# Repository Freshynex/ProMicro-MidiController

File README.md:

# Pro Micro Midi Controller

## 1. A projekt bemutatása
### 1.1 Általános leírás
Ez a projekt a zenekészítés/zeneszerzés folyamatát segíti a MIDI protokoll felhasználásával.
Ennek a készüléknek a felépítése különböző feladatott ellátó alrészekből áll.

### 1.2 Vezérlő és modulok

A legfőbb része egy Atmel ATMEGA32u4 ic-vel ellátott Arduino Pro Micro fejlesztői alaplap (továbbiakban MCU).
Az MCU-t egy kifejtő-kártyára helyezve a többi alrész (továbbiakban modul) ráköthető.

A kifejtőkártya:

A következő modulok vannak integrálva a készülékben:

 - Kijelző modul (továbbiakban <b>DISP</b>), amely egy egyszerű interfészt biztosít, hogy az aktuális bemeneti
értékeket visszaadja, illetve hogy kényelmesen lehessen konfigurálni azt.

 - Oktáv-váltó modul (továbbiakban <b>OCTSTP</b>), amely egyszerű elérhetőséget ad oktáv-léptetéshez
  
 - Analóg modul (továbbiakban <b>ANAL</b>), egy olyan felület amely kihasználja az MCU saját analog bemeneteit, és
visszaad egy értéket.

 - Billentyűzet modul (továbbiakban <b>KB</b>), amely egy 2 oktávos zongora interfészt ad a felhasználónak. 

## 2. Alkatrészek és kapcsolás

### 2.1 Főalkatrészek

MCU: Arduino Pro Micro Atmel ATMEGA32u4

DISP: 128x64 i2c oled display (SSD1306 driver)

Oktáv váltó gombok: TACTS-6x6x7.3 (2 db)

KB gombok: AKKO Stellar Rose Switch – Lubed-5pin (24 db)

Tengelyes potméter: POM1615 LIN 1K B (2 db)

Toló potméter: PTA2043-2015CIB203 (2 db)

PISO shift register: 74HC166 (3 db)

### 2.1 Kapcsolás rajz

## 3. Funkcionalitás
 Teszteléshez használt szoftver: FL Studio 20 (Macbook M1-en kicsit bugos, ezért a kép villódzik néha)

### 3.1 MIDI Protokoll

A MIDI protokollban 8 bites adatcsomagokkal dolgozunk. Két féle üzenet van: status és data. Az első bit azt jelöli, hogy a kettő közül melyiket küldjük, így adat üzenet esetén 0-127, command üzenet esetén 128-255 a használható értéktartomány. Ezek együttesen alkotnak egy midi üzenetet (message).

Egy üzenet mindig status byte-tal kezdődik, amit a parancs függvényében 0, 1 vagy 2 data byte követ.
A status byte felső 4 bitje jelöli a kiadott parancsot (aminek az első bitje mindig 1, így az első kódszó decimálisan a 8), a második fele a csatornát jelöli (16 csatornát lehet kezelni, ebben a projektben egynél többre nincs szükségünk).

Számunkra fontosabb status üzenetek:

| Status üzenet  | Üzenet kódja | Adat byte 1 | Adat byte 2 | Adat byte 3 |
| -------------  | ------------ | ----------- | ----------- | ----------- |
| NoteOn         | 0x90         | Pitch       | Velocity    |             |
| NoteOff        | 0x80         | Pitch       | Velocity    |             |
| Control Change | 0xB0         | CC number   | MSB         | LSB *       | 

 *<sub> Adat byte 3 (LSB) nem kötelező, de 7 helyett 14 bit pontosságu értéket adhatunk meg vele </sub>

### 3.2 Billentyűzet

A billentyűzet kialakítása egy zongora mintájára készült. 2 oktáv, ami 24 gomb. A gombok mechanikus billentyűkapcsolókkal vannak kivitelezve. A keret illetve gomb kupakok 3D nyomtatással készültek. Három kaszkádolt parallel in serial out shift register segítségével vannak az MCU-ra kötve, így csak 3 pin felhasználása szükséges. Ez a fajta megoldás lehetővé teszi hogy 3Byte-on visszakapjuk a gombok állapotát egyszerre.

### 3.3 Oktáv váltás

A zenekészítéshez szükséges, hogy a billentyűzet képes legyen több oktávon is játszani. Ehhez az <b>MCU</b> két digitális bemenetét használjuk. A készülék oktáv-váltó gombok hatására a billentyűzeten reprezentált 2 oktávot eltolja, és így mind a 10 MIDI protokollban használt oktáv elérhető.

### 3.4 Analog bevitel

Kettő forgatható és kettő tolható lineáris potméter segítségével, kihasználva Kirchoff törvényeit, képes a készülék adott csatornák állapotait módosítani. A választott <b>MCU</b> analog bemenetei a referencia feszültséghez képest adja vissza a bemeneti értéket. Ezt a készülék 0-1023-as intervallumban elhelyezi (map-eli).

Ez a következő képpen nyílvánul meg:
| Ref. V         | ANAL bemenet | Érték       |
| -------------  | ------------ | ----------- |
|       5V       | 0V           | 0           |
|       -"-      | 2.5V         | 512         |
|       -"-      | 5V           | 1023        |

### 3.5 i²c Kijelző és protokol

Az i²c, egy olyan protokoll, amely MASTER-SLAVE kapcsolatot biztosít <u>kettő vagy több</u> eszköz között. A szállítandó adatot a protokoll címkézi és szállítja az adatvonalon.
Amikor a SLAVE címe egyezik a csomagban elhelyezett célcímmel, akkor azt a SLAVE fogadja és feldogozza. 

A készülék rendelkezik egy kis 1.2"-es OLED kijelző, amely SSD1306-os meghajtású. Jelenleg a <b>DISP</b> beépített címmel rendelkezik, amelynek a módosítása nehézkes.
A mostani címe <b>0x78</b>.

## 4. Bővithetőség
### 4.1 I²C (Inter-Integrated Circuit)

Az <b>MCU</b>-nak nem az összes pin-jét használtuk, ezért ezekre még kapcsolhatóak eszközök. Amennyiben a beépítendő eszköz i²c-vel kommunikál, így az ráközhető párhuzamosan ugyanarra az ágra, amelyiken rajta van a <b>DISP</b>. Ebben az esetben érdemes figyelni a rákötendő eszköz <u><b>címére</b></u>. Amennyiben a címeknél ütközés történik, úgy nem fog működik a ráhelyezett eszköz, illetve a <b>DISP</b>.

Lehetséges bővítési lehetőségek a jelzett protokollon:
| IC / MODUL név | Funkció                  |
| -------------  | ------------------------ |
|  ADS1115 / -M  | ANAL bővítő (A0 - A3)    |
|PCF8574 / IN830S| DIGITAL bővítő (8db, be) |
|PCF8574 / OC805S| DIGITAL bővítő (8db, ki) |

### 4.2 UART (Universal Asynchronous Receiver-Transmitter)

Az UART egy olyan soron protokoll fajta, amely két egyenrangú eszközt köt össze. Bekötéséhez egy adó, egy fogadó és közös test szükséges. Ez a protokoll a közlendő információt egy start- és stop-bittel ellátott bitfolyammá alakítja.
Ehhez a fajta kapcsolathoz nem szükséges külön órajel, mivel a kommunikációt egy közösen előre deklarált jelaránnyal (baudrate) éri el. A Küldő fél a bitfolyamot a saját Tx (Transmit) ágán küldi a másik eszköz Rx (Receive lábára.
Ez igaz fordítottan is, ezért ez a fajta megoldás Full-Duplex-nek minősül.
| A eszköz | B eszköz |
|----------|----------|
|    Tx    |    Rx    |
|    Rx    |    Tx    |
|    G     |    G     |
|   *Vcc   |   *Vcc   |

*<sub>Ha a másik készülék rendelkezik saját táp-ellátással, akkor a Vcc összekötése nem szükséges.</sub>

## 5. Készülék Prezentáció és Demo

### Billentyűzet
https://github.com/user-attachments/assets/6a722bac-2a85-4638-812b-2556ad7aba79

### Potméter
[<video src="_vids/Pot_demo.mp4" width="320" height="240" controls></video>
](https://github.com/user-attachments/assets/77403d33-6a48-4602-aa05-ce928a655359
)
### Billentyűzet, potméter (pitch paraméter állítása), oktáv váltás
https://github.com/user-attachments/assets/33ad1122-0a03-4d51-aa62-576f443cc43e

### 3D render

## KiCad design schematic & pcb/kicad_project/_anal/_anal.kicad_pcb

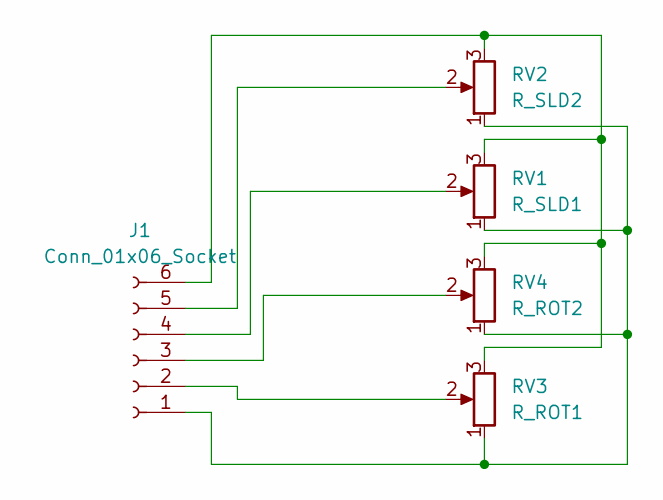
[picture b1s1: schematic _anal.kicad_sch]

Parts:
J1: Conn_01x06_Socket; PinSocket_1x06_P2.54mm_Vertical
RV1: R_SLD1; Potentiometer_Bourns_PTA4543_Single_Slide
RV2: R_SLD2; Potentiometer_Bourns_PTA4543_Single_Slide
RV3: R_ROT1; PinSocket_1x03_P2.54mm_Vertical
RV4: R_ROT2; PinSocket_1x03_P2.54mm_Vertical

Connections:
unnamed: J1.1, RV1.1, RV2.1, RV3.1, RV4.1
unnamed: J1.2, RV3.2
unnamed: J1.3, RV4.2
unnamed: J1.4, RV1.2
unnamed: J1.5, RV2.2
unnamed: J1.6, RV1.3, RV2.3, RV3.3, RV4.3

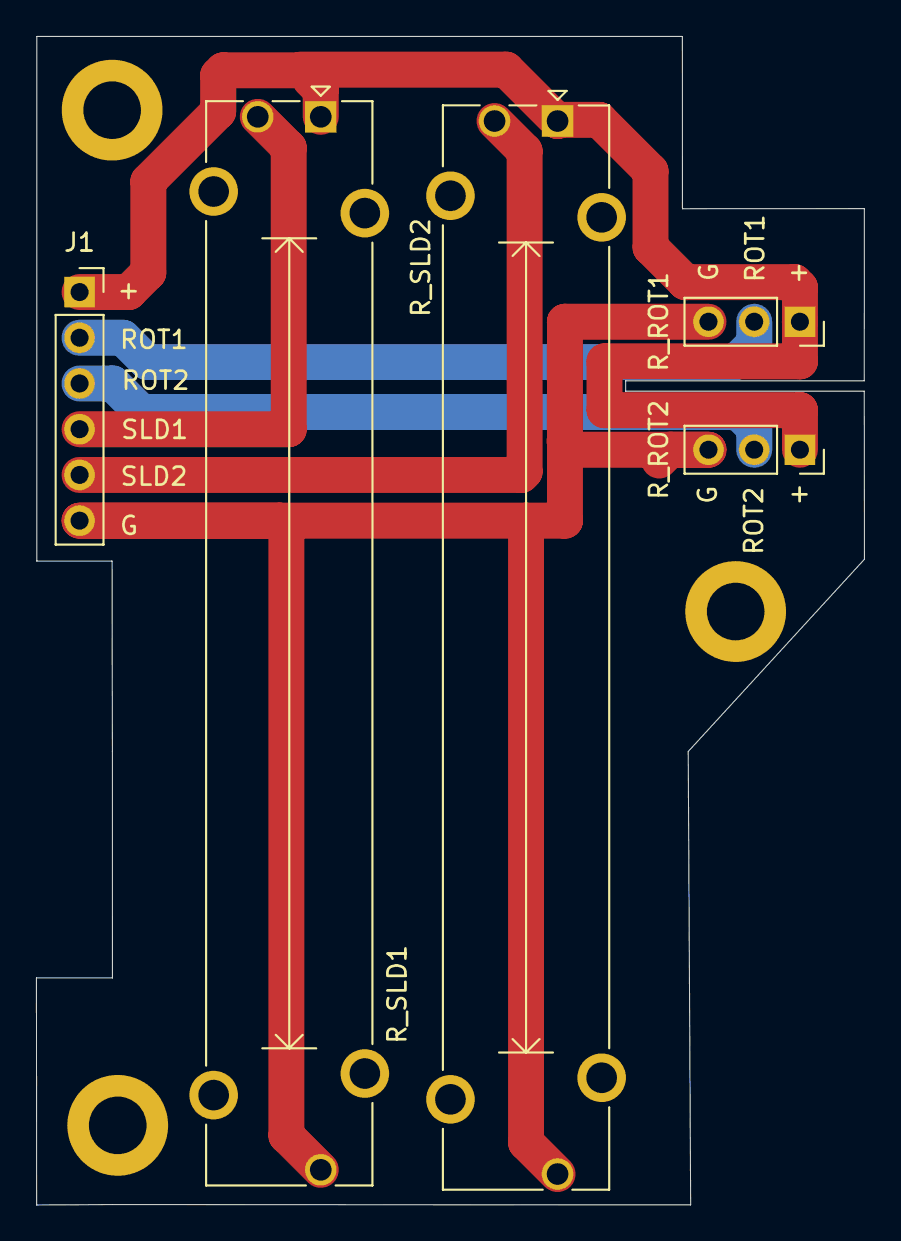
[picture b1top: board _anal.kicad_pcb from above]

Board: 2 copper layers, 46.0 x 64.9 mm, 5 parts (0 on the bottom side), 6 nets.

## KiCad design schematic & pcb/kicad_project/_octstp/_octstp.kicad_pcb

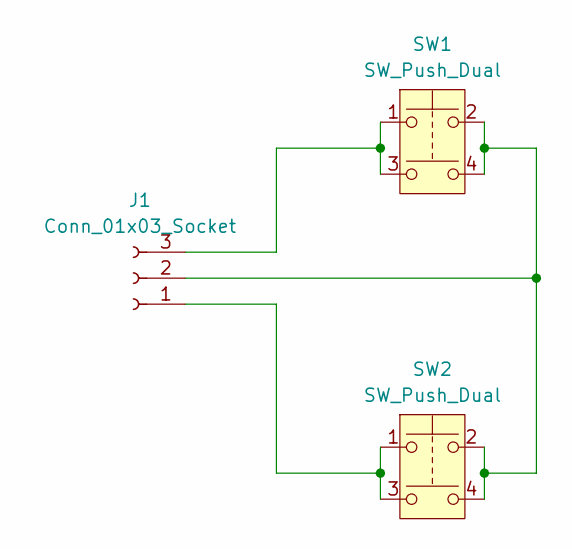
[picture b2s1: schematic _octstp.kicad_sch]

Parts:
J1: Conn_01x03_Socket; PinSocket_1x03_P2.54mm_Vertical
SW1, SW2: SW_Push_Dual; SW_PUSH-12mm

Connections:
unnamed: J1.1, SW2.1, SW2.3
unnamed: J1.2, SW1.2, SW1.4, SW2.2, SW2.4
unnamed: J1.3, SW1.1, SW1.3

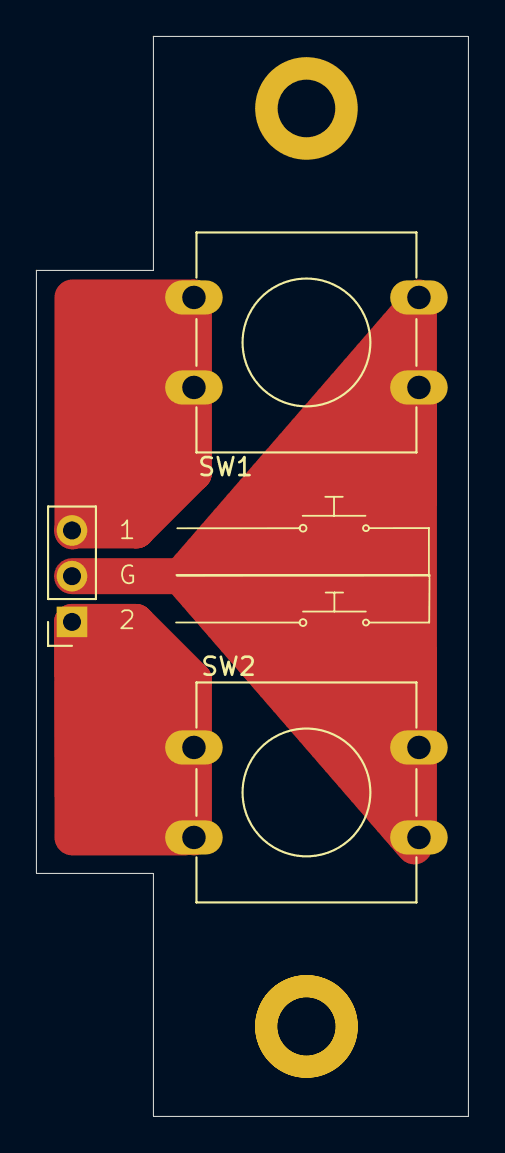
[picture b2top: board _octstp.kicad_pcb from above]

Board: 2 copper layers, 24.0 x 60.0 mm, 3 parts (0 on the bottom side), 3 nets.

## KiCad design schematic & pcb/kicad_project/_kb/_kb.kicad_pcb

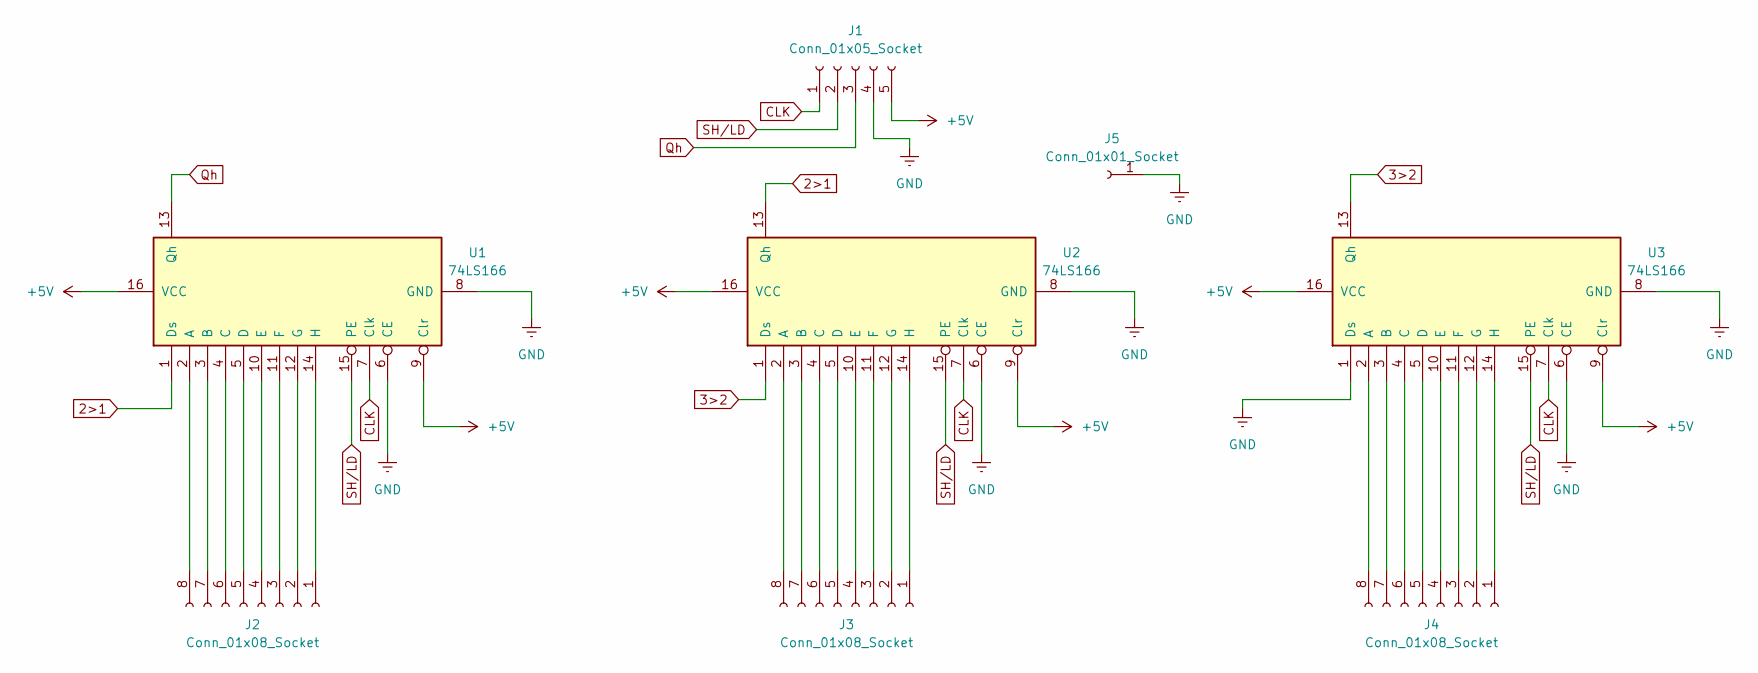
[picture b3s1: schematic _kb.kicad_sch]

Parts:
J1: Conn_01x05_Socket; PinSocket_1x05_P2.54mm_Vertical
J2, J3, J4: Conn_01x08_Socket; PinSocket_1x08_P2.54mm_Vertical
J5: Conn_01x01_Socket; PinSocket_1x01_P2.54mm_Vertical
U1, U2, U3: 74LS166; DIP-16_W7.62mm_Socket

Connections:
2>1: U1.1 (Ds), U2.13 (Qh)
3>2: U2.1 (Ds), U3.13 (Qh)
+5V: J1.5, U1.9 (Clr), U1.16 (VCC), U2.9 (Clr), U2.16 (VCC), U3.9 (Clr), U3.16 (VCC)
CLK: J1.1, U1.7 (Clk), U2.7 (Clk), U3.7 (Clk)
GND: J1.4, J5.1, U1.6 (CE), U1.8 (GND), U2.6 (CE), U2.8 (GND), U3.1 (Ds), U3.6 (CE), U3.8 (GND)
unnamed: J2.1, U1.14 (H)
unnamed: J2.2, U1.12 (G)
unnamed: J2.3, U1.11 (F)
unnamed: J2.4, U1.10 (E)
unnamed: J2.5, U1.5 (D)
unnamed: J2.6, U1.4 (C)
unnamed: J2.7, U1.3 (B)
unnamed: J2.8, U1.2 (A)
unnamed: J3.1, U2.14 (H)
unnamed: J3.2, U2.12 (G)
unnamed: J3.3, U2.11 (F)
unnamed: J3.4, U2.10 (E)
unnamed: J3.5, U2.5 (D)
unnamed: J3.6, U2.4 (C)
unnamed: J3.7, U2.3 (B)
unnamed: J3.8, U2.2 (A)
unnamed: J4.1, U3.14 (H)
unnamed: J4.2, U3.12 (G)
unnamed: J4.3, U3.11 (F)
unnamed: J4.4, U3.10 (E)
unnamed: J4.5, U3.5 (D)
unnamed: J4.6, U3.4 (C)
unnamed: J4.7, U3.3 (B)
unnamed: J4.8, U3.2 (A)
Qh: J1.3, U1.13 (Qh)
SH/LD: J1.2, U1.15 (PE), U2.15 (PE), U3.15 (PE)

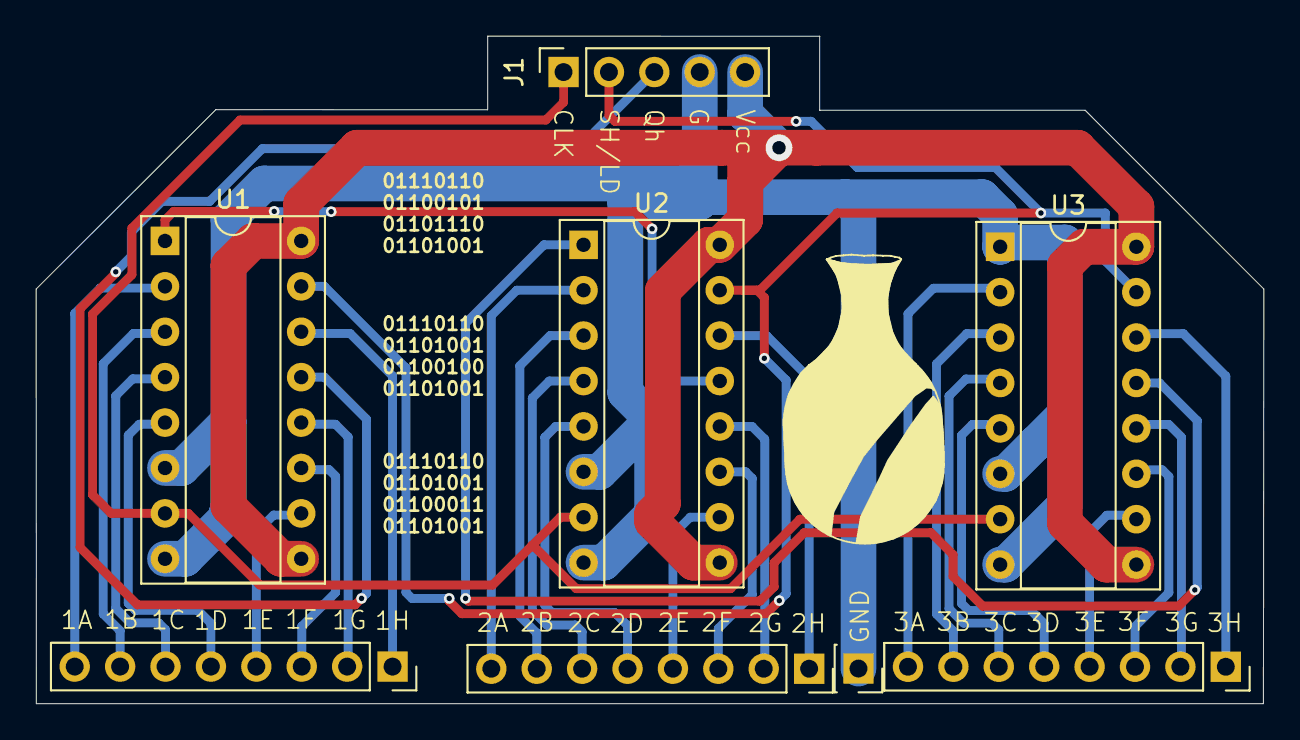
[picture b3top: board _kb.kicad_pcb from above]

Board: 2 copper layers, 68.7 x 37.3 mm, 8 parts (0 on the bottom side), 31 nets.

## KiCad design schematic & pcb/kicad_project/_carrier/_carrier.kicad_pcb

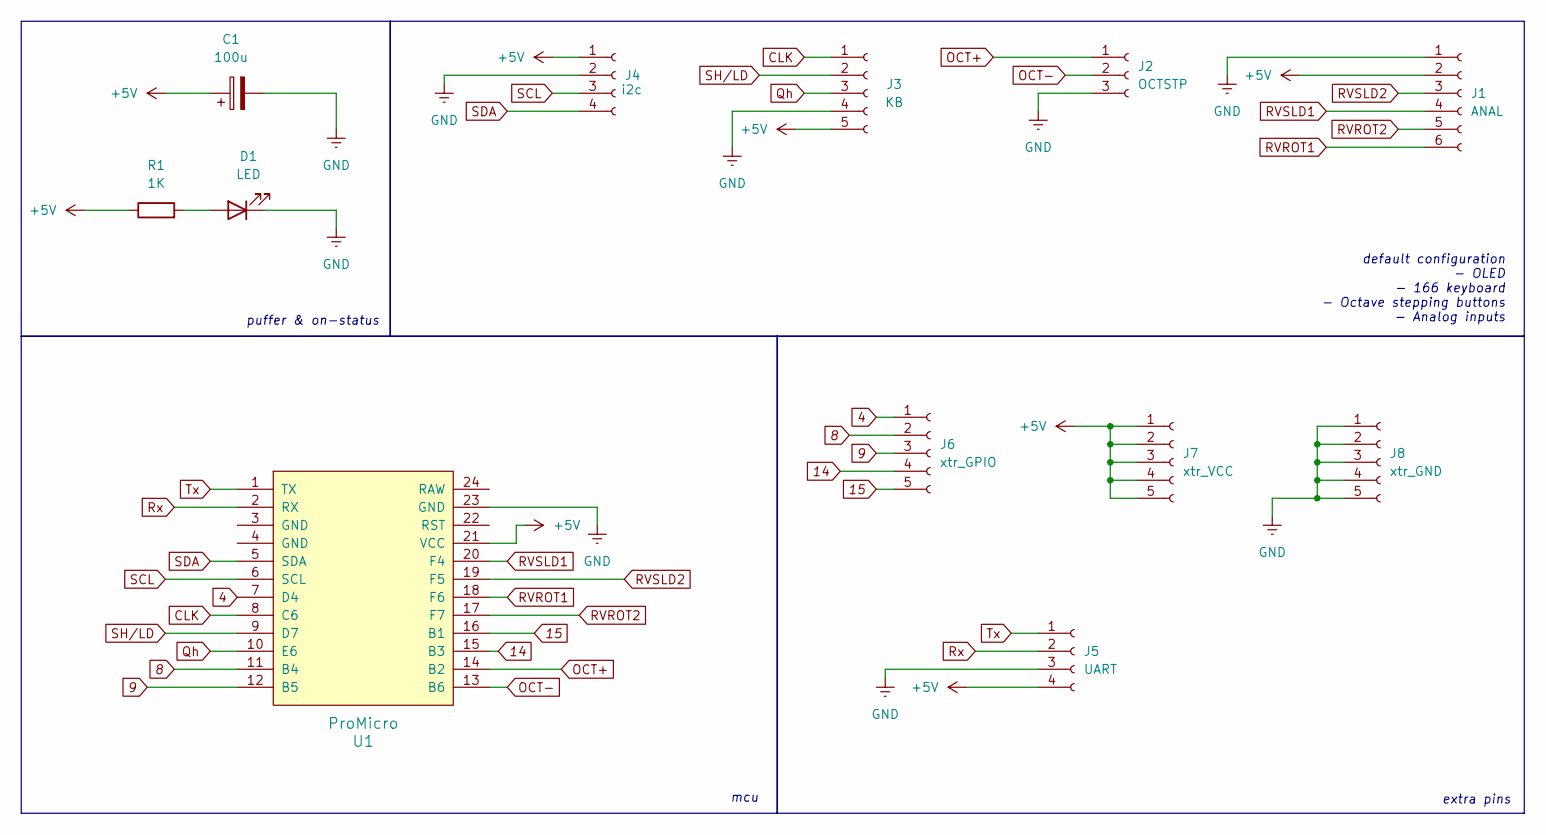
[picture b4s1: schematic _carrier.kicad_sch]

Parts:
C1: 100u; CP_Radial_D10.0mm_P5.00mm
D1: LED; LED_D5.0mm
J1: ANAL; PinSocket_1x06_P2.54mm_Vertical
J2: OCTSTP; PinSocket_1x03_P2.54mm_Vertical
J3: KB; PinSocket_1x05_P2.54mm_Vertical
J4: i2c; PinSocket_1x04_P2.54mm_Vertical
J5: UART; PinSocket_1x04_P2.54mm_Vertical
J6: xtr_GPIO; PinSocket_1x05_P2.54mm_Vertical
J7: xtr_VCC; PinSocket_1x05_P2.54mm_Vertical
J8: xtr_GND; PinSocket_1x05_P2.54mm_Vertical
R1: 1K; R_Axial_DIN0309_L9.0mm_D3.2mm_P12.70mm_Horizontal
U1: ProMicro

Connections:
4: J6.1, U1.7 (D4)
8: J6.2, U1.11 (B4)
9: J6.3, U1.12 (B5)
14: J6.4, U1.15 (B3)
15: J6.5, U1.16 (B1)
+5V: C1.1, J1.2, J3.5, J4.1, J5.4, J7.1, J7.2, J7.3, J7.4, J7.5, R1.1, U1.21 (VCC)
CLK: J3.1, U1.8 (C6)
GND: C1.2, D1.1 (K), J1.1, J2.3, J3.4, J4.2, J5.3, J8.1, J8.2, J8.3, J8.4, J8.5, U1.23 (GND)
unnamed: D1.2 (A), R1.2
OCT+: J2.1, U1.14 (B2)
OCT-: J2.2, U1.13 (B6)
Qh: J3.3, U1.10 (E6)
RVROT1: J1.6, U1.18 (F6)
RVROT2: J1.5, U1.17 (F7)
RVSLD1: J1.4, U1.20 (F4)
RVSLD2: J1.3, U1.19 (F5)
Rx: J5.2, U1.2 (RX)
SCL: J4.3, U1.6 (SCL)
SDA: J4.4, U1.5 (SDA)
SH/LD: J3.2, U1.9 (D7)
Tx: J5.1, U1.1 (TX)

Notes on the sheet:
default configuration - OLED - 166 keyboard - Octave stepping buttons - Analog inputs
mcu
extra pins
puffer & on-status

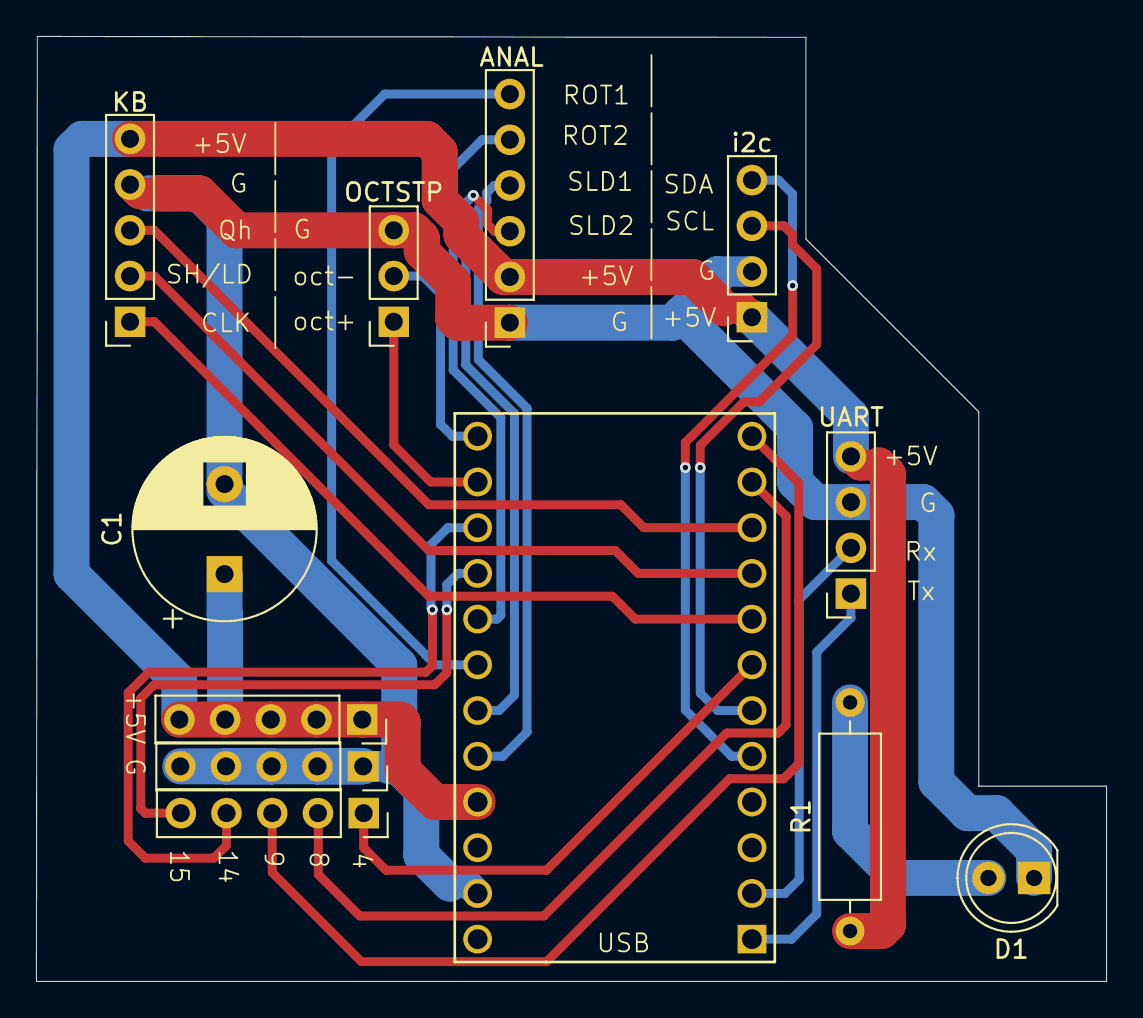
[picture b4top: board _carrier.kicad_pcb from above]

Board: 2 copper layers, 59.5 x 52.5 mm, 12 parts (0 on the bottom side), 21 nets.

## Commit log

2026-04-06 pinout image added
2026-04-25 képek (SESSION_2026-04-25)
    2025-06-25 (egésznapos)
    -haladás dokumentációja képek formájában
2026-04-25 átnevezés 2026-04-25
2026-04-26 SCHEMATIC 2026-04-26
    KiCAD 8.0-ban készített projekt
    - kapcsolási rajz a 2 oktávos billentyűzet nélkül rövid leírásokkal. (ANGOL, ellenőrizni kell)
    - exportált pdf
2026-04-26 dark schematic export 2026-04-26
2026-04-26 SCHEMATIC UPDATE 2026-04-27
    - kapcsolási rajz frissítve (keyboard)
2026-05-16 Rename Screenshot 2026-05-16 at 21.01.59.png to Schematic
2026-05-16 Rename Schematic to Schematic.png
2026-05-18 Update README.md
    nézdmajdmeg
2026-05-18 Update README.md
    csekkcsekk
2026-05-18 Update README.md
    faszom
2026-05-18 Update README.md
    csakcsakkészleszmárbasszameg
2026-05-20 Update README.md
    nan
2026-05-20 Update README.md
    asd
2026-05-23 vids
    faszooom
2026-05-23 Rename 20260523_023652.mp4 to Keyboard pitch wheel octave demo.mp4
2026-05-29 Update README.md
    Csak legyen már akkor benne az UART gecixd
2026-05-29 Update README.md
    na most gecixd
2026-05-29 Update README.md
    faszomat
2026-05-29 1st pcb plan devboard like
    1:30 AM GECIII
2026-05-29 dik
    anyadat 3d
2026-05-29 miagecim
2026-05-30 keyboard pcb
2026-05-30 octstep schematic and pcb
2026-05-30 fuuuuu sok minden, majd csekkold
2026-06-07 missed pushes
2026-06-07 pics mkoa
2026-06-07 front update pics
